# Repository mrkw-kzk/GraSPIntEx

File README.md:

# Gra&SP Int. Ex.

## !!!! CAUTION !!!!
These files are not verified.
Its silk is deliberately too little.

### Use These
- SparkFun Qwiic Pro Micro https://www.sparkfun.com/products/15795
- molex 955016449 https://www.molex.com/molex/products/part-detail/modular_jacks_plug/0955016449
- Diodes 1N4148W https://www.diodes.com/part/view/1N4148W
- YAGEO RC0603FR-074K7P https://www.yageo.com/en/ProductSearch/PartNumberSearch?part_number=RC0603FR-074K7P
- Your beloved CherryMX Compatible Keys
- Keycaps that fit your hands
- 4P4C RJ-9 Cable you like
- Extreme super speed USB-C cable
- Stylish M3 screws
- Cool M3 x 7mm or more spacers
- Unwavering rubber feet
- A heart that never gives up

#### How to Make
Pin-1s and cathodes have silk dots.
See the tweets: https://twitter.com/AEtheR3can/status/1475350572333400072?s=20

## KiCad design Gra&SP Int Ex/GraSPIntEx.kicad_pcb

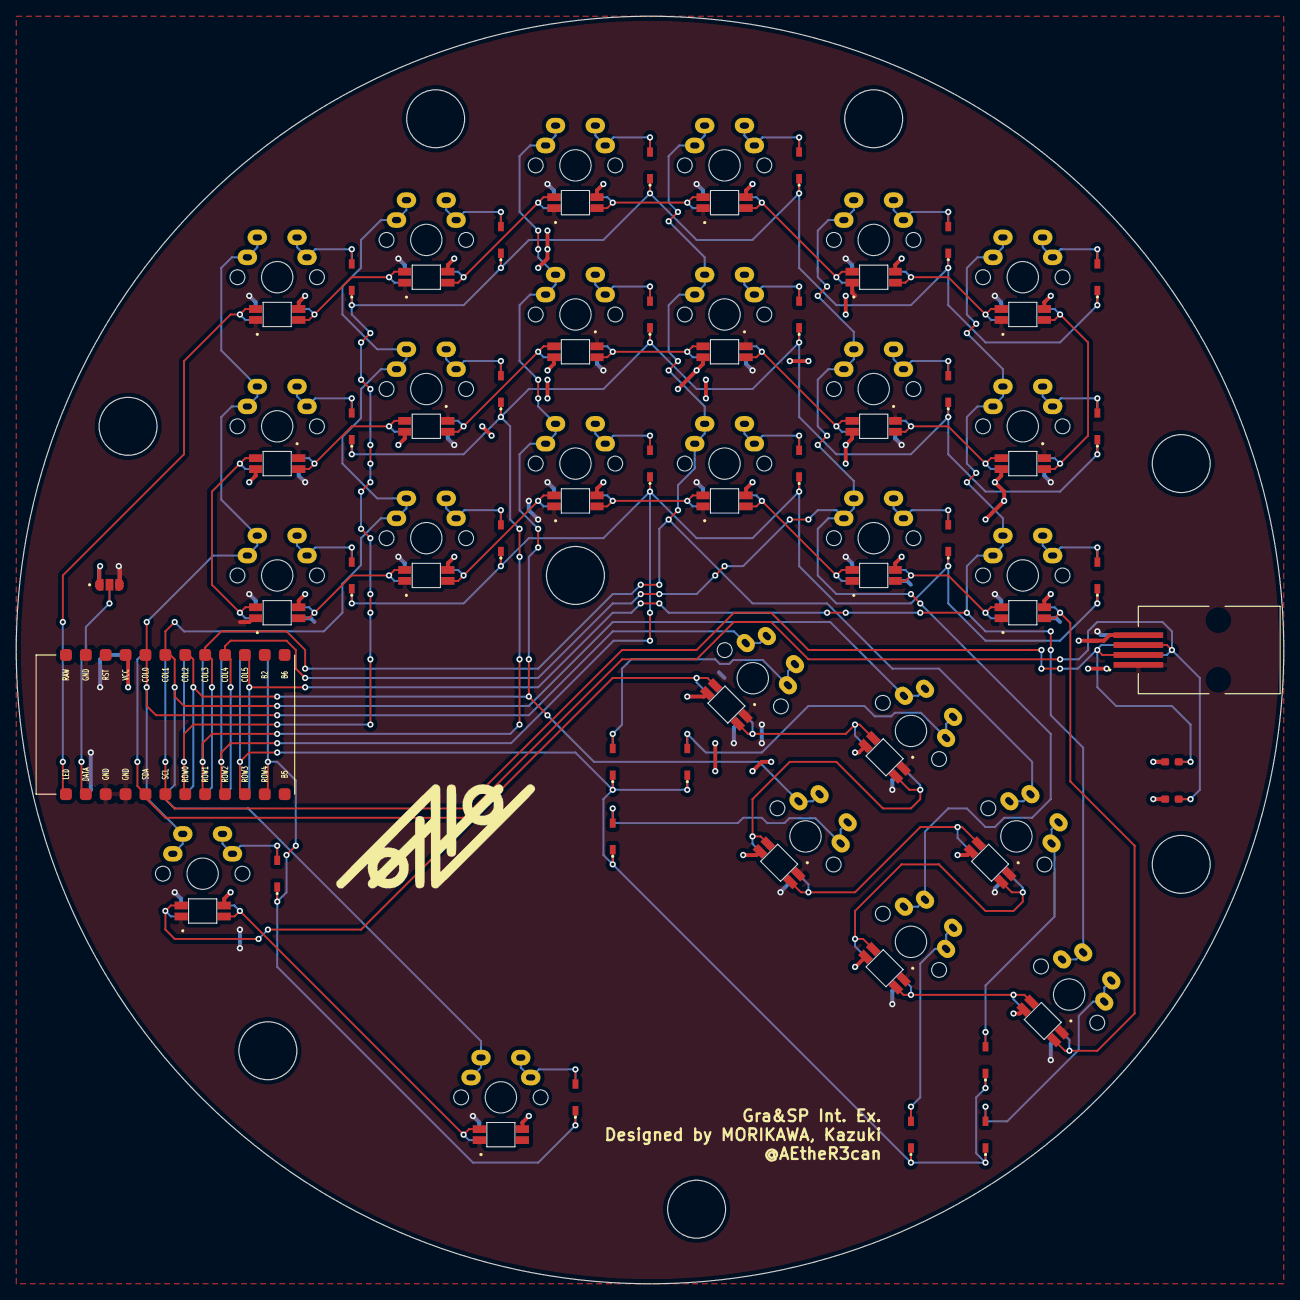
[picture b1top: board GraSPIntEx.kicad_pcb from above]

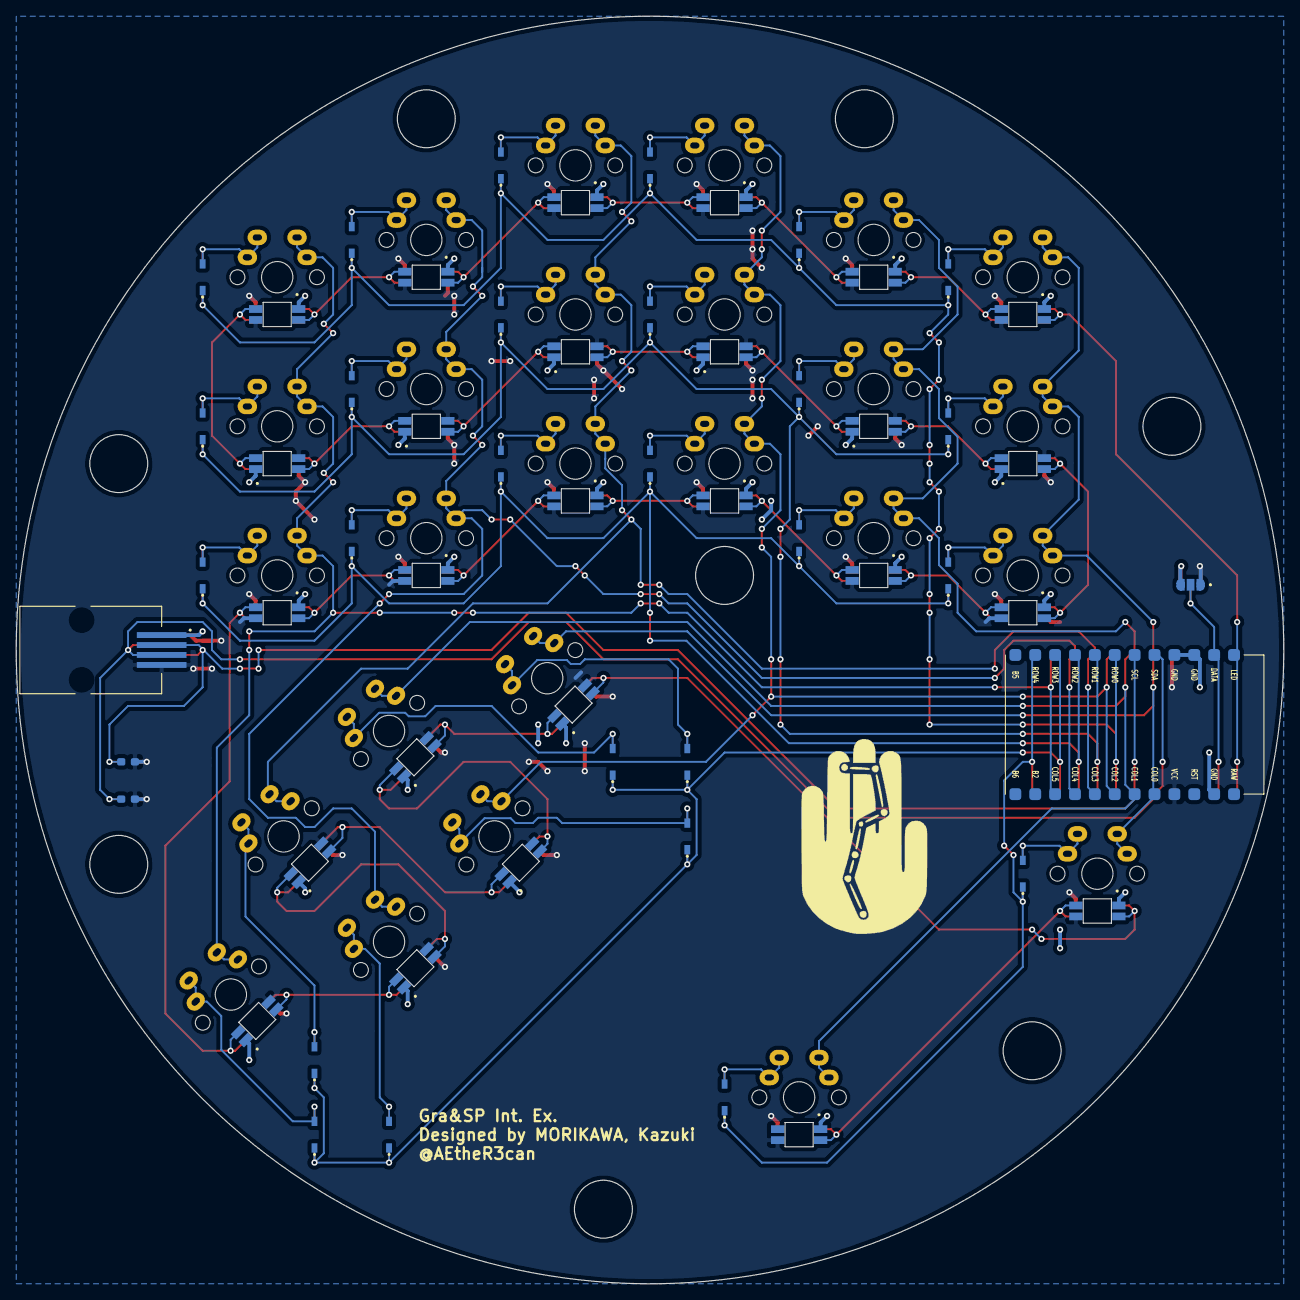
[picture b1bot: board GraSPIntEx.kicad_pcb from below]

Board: 2 copper layers, 161.9 x 161.9 mm, 142 parts (58 on the bottom side), 68 nets.

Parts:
D1, D2, D3, D4, D5, D6, D7, D8, D9, D10, D11, D12, D13, D14, D15, D16, D17, D18, D19, D20, D21, D22, D23, D24, D25, D26, D27, D28, D29, D30, D31, D32, D33, D34, D35, D36, D37, D38, D39, D40, D41, D42, D43, D44, D45, D46, D47, D48, D49, D50, D51, D52: D
G1: LOGO; aether
G2: LOGO; grasp
J1: 4P4C; 4P4C_SMD
J2: 4P4C; 4P4C_SMD_wo_hole
JP1, JP2: SolderJumper_3_Open; SolderJumper-3
LED1, LED2, LED3, LED4, LED5, LED6, LED7, LED8, LED9, LED10, LED11, LED12, LED13, LED14, LED15, LED16, LED17, LED18, LED19, LED20, LED21, LED22, LED23, LED24, LED25, LED26: YS-SK6812MINI-E
LED27, LED28, LED29, LED30, LED31, LED32, LED33, LED34, LED35, LED36, LED37, LED38, LED39, LED40, LED41, LED42, LED43, LED44, LED45, LED46, LED47, LED48, LED49, LED50, LED51, LED52: YS-SK6812MINI-E; YS-SK6812MINI-E_wo_edge_cut
R1, R2, R3, R4: R
SW1, SW2, SW3, SW4, SW5, SW6, SW7, SW8, SW9, SW10, SW11, SW12, SW13, SW14, SW15, SW16, SW17, SW18, SW19, SW20, SW21, SW22, SW23, SW24, SW25, SW26: SW_PUSH; CherryMX_1u_r
U1, U2: Qwiic Pro Micro; Qwiic_ProMicro_SMD

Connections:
GND: J1.1, J2.1, JP1.3, JP2.3, LED1.3, LED2.3, LED3.3, LED4.3, LED5.3, LED6.3, LED7.3, LED8.3, LED9.3, LED10.3, LED11.3, LED12.3, LED13.3, LED14.3, LED15.3, LED16.3, LED17.3, LED18.3, LED19.3, LED20.3, LED21.3, LED22.3, LED23.3, LED24.3, LED25.3, LED26.3, LED27.3, LED28.3, LED29.3, LED30.3, LED31.3, LED32.3, LED33.3, LED34.3, LED35.3, LED36.3, LED37.3, LED38.3, LED39.3, LED40.3, LED41.3, LED42.3, LED43.3, LED44.3, LED45.3, LED46.3, LED47.3, LED48.3, LED49.3, LED50.3, LED51.3, LED52.3, U1.3, U1.4, U1.23, U2.3, U2.4, U2.23
LED_IN: LED1.4, LED27.4, U1.1, U2.1
unnamed: D1.2, D2.2, SW1.2
unnamed: D3.2, D4.2, SW2.2
unnamed: D5.2, D6.2, SW3.2
unnamed: D7.2, D8.2, SW4.2
unnamed: D9.2, D10.2, SW5.2
unnamed: D11.2, D12.2, SW6.2
unnamed: D13.2, D14.2, SW7.2
unnamed: D15.2, D16.2, SW8.2
unnamed: D17.2, D18.2, SW9.2
unnamed: D19.2, D20.2, SW10.2
unnamed: D21.2, D22.2, SW11.2
unnamed: D23.2, D24.2, SW12.2
unnamed: D25.2, D26.2, SW13.2
unnamed: D27.2, D28.2, SW14.2
unnamed: D29.2, D30.2, SW15.2
unnamed: D31.2, D32.2, SW16.2
unnamed: D33.2, D34.2, SW17.2
unnamed: D35.2, D36.2, SW18.2
unnamed: D37.2, D38.2, SW19.2
unnamed: D39.2, D40.2, SW20.2
unnamed: D41.2, D42.2, SW21.2
unnamed: D43.2, D44.2, SW22.2
unnamed: D45.2, D46.2, SW23.2
unnamed: D47.2, D48.2, SW24.2
unnamed: D49.2, D50.2, SW25.2
unnamed: D51.2, D52.2, SW26.2
unnamed: LED1.2, LED2.4, LED27.2, LED28.4
unnamed: LED2.2, LED3.4, LED28.2, LED29.4
unnamed: LED10.2, LED11.4, LED36.2, LED37.4
unnamed: LED9.2, LED10.4, LED35.2, LED36.4
unnamed: LED11.2, LED12.4, LED37.2, LED38.4
unnamed: LED12.2, LED13.4, LED38.2, LED39.4
unnamed: LED13.2, LED14.4, LED39.2, LED40.4
unnamed: LED14.2, LED15.4, LED40.2, LED41.4
unnamed: LED15.2, LED16.4, LED41.2, LED42.4
unnamed: LED16.2, LED17.4, LED42.2, LED43.4
unnamed: LED17.2, LED18.4, LED43.2, LED44.4
unnamed: LED18.2, LED19.4, LED44.2, LED45.4
unnamed: LED19.2, LED20.4, LED45.2, LED46.4
unnamed: LED20.2, LED21.4, LED46.2, LED47.4
unnamed: LED21.2, LED22.4, LED47.2, LED48.4
unnamed: LED22.2, LED23.4, LED48.2, LED49.4
unnamed: LED23.2, LED24.4, LED49.2, LED50.4
unnamed: LED24.2, LED25.4, LED50.2, LED51.4
unnamed: LED25.2, LED26.4, LED51.2, LED52.4
unnamed: LED3.2, LED4.4, LED29.2, LED30.4
unnamed: LED4.2, LED5.4, LED30.2, LED31.4
unnamed: LED5.2, LED6.4, LED31.2, LED32.4
unnamed: LED6.2, LED7.4, LED32.2, LED33.4
unnamed: LED7.2, LED8.4, LED33.2, LED34.4
unnamed: LED8.2, LED9.4, LED34.2, LED35.4
RX1: JP1.2, JP2.2, U1.2, U2.2
SCL: J1.2, J2.2, R1.2, R3.2, U1.6, U2.6
SDA: J1.3, J2.3, R2.2, R4.2, U1.5, U2.5
VCC: J1.4, J2.4, JP1.1, JP2.1, LED1.1, LED2.1, LED3.1, LED4.1, LED5.1, LED6.1, LED7.1, LED8.1, LED9.1, LED10.1, LED11.1, LED12.1, LED13.1, LED14.1, LED15.1, LED16.1, LED17.1, LED18.1, LED19.1, LED20.1, LED21.1, LED22.1, LED23.1, LED24.1, LED25.1, LED26.1, LED27.1, LED28.1, LED29.1, LED30.1, LED31.1, LED32.1, LED33.1, LED34.1, LED35.1, LED36.1, LED37.1, LED38.1, LED39.1, LED40.1, LED41.1, LED42.1, LED43.1, LED44.1, LED45.1, LED46.1, LED47.1, LED48.1, LED49.1, LED50.1, LED51.1, LED52.1, R1.1, R2.1, R3.1, R4.1, U1.21, U2.21
X0: SW1.1, SW7.1, SW13.1, SW19.1, SW25.1, U1.20, U2.20
X1: SW2.1, SW8.1, SW14.1, SW20.1, SW26.1, U1.19, U2.19
X2: SW3.1, SW9.1, SW15.1, SW21.1, U1.18, U2.18
X3: SW4.1, SW10.1, SW16.1, SW22.1, U1.17, U2.17
X4: SW5.1, SW11.1, SW17.1, SW23.1, U1.16, U2.16
X5: SW6.1, SW12.1, SW18.1, SW24.1, U1.15, U2.15
Y0: D1.1, D2.1, D3.1, D4.1, D5.1, D6.1, D7.1, D8.1, D9.1, D10.1, D11.1, D12.1, U1.7, U2.7
Y1: D13.1, D14.1, D15.1, D16.1, D17.1, D18.1, D19.1, D20.1, D21.1, D22.1, D23.1, D24.1, U1.8, U2.8
Y2: D25.1, D26.1, D27.1, D28.1, D29.1, D30.1, D31.1, D32.1, D33.1, D34.1, D35.1, D36.1, U1.9, U2.9
Y3: D37.1, D38.1, D39.1, D40.1, D41.1, D42.1, D43.1, D44.1, D45.1, D46.1, D47.1, D48.1, U1.10, U2.10
Y4: D49.1, D50.1, D51.1, D52.1, U1.11, U2.11

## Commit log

2021-04-25 move
2021-10-13 pcbfiles
2021-12-15 Printed
